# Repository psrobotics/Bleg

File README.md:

# Bleg

Open-source, low cost quadruped leg design with BLDC actuator.

## Videos

[Leg](https://www.youtube.com/watch?v=UqaFMdyX_vk)  /  [Reducer](https://www.youtube.com/watch?v=V_eoM8oxp7Y)

## File Structure

* /hardware - CAD, STL exports, CAM file

* /electronic - Motor driver(Odrive v3.6), Main controller brd, Encoder brd

* /sim - V-rep simulation, python wrapper

## Pics

### Reducer

### Encoder

### Motor

### Parts

## Leg assembly

## License
MIT License

## Contact
* Shuang Peng, {shuangpe}@usc.edu

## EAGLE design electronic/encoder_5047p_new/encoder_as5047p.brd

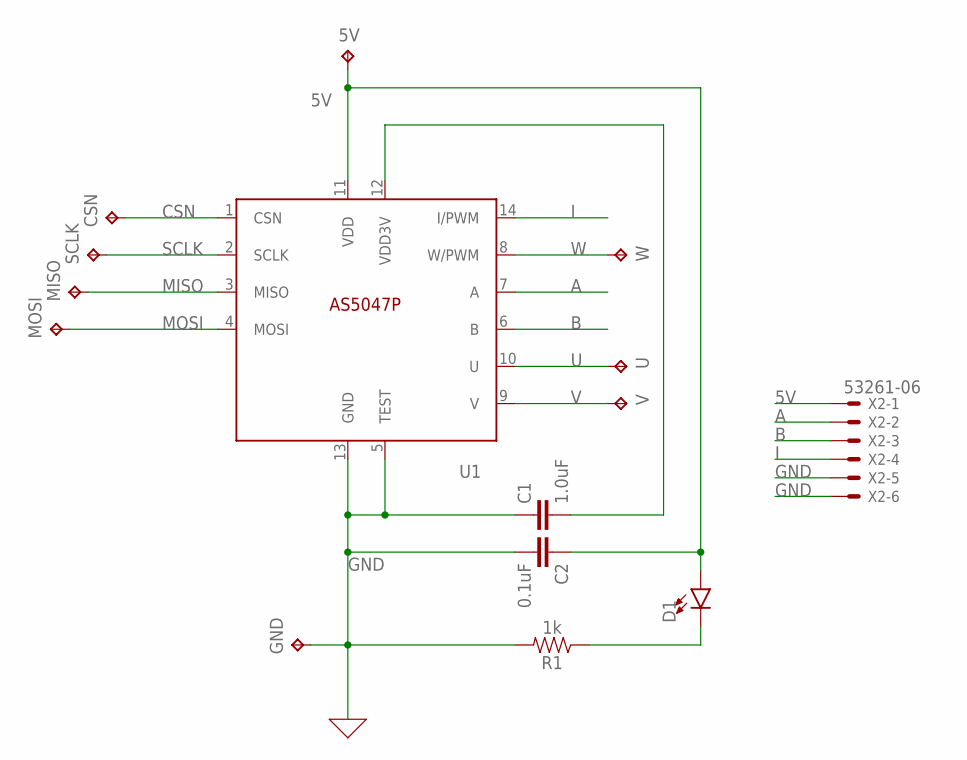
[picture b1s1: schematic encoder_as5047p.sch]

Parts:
5V: TPTP12R; TP12R
C1: 1.0uF; 0603
C2: 0.1uF; 0603
CSN: TPTP12R; TP12R
D1: LED0603; LED-0603
GND: TPTP12R; TP12R
MISO: TPTP12R; TP12R
MOSI: TPTP12R; TP12R
R1: 1k; 0603
SCLK: TPTP12R; TP12R
U: TPTP12R; TP12R
U1: AS5047P; TSSOP14
V: TPTP12R; TP12R
W: TPTP12R; TP12R
X2: 53261-06

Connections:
5V: 5V.TP, C2.1, D1.A, U1.11 (VDD), X2.1
A: U1.7 (A), X2.2
B: U1.6 (B), X2.3
CSN: CSN.TP, U1.1 (CSN)
GND: C1.1, C2.2, GND.TP, R1.2, U1.5 (TEST), U1.13 (GND), X2.5, X2.6
I: U1.14 (I/PWM), X2.4
MISO: MISO.TP, U1.3 (MISO)
MOSI: MOSI.TP, U1.4 (MOSI)
unnamed: C1.2, U1.12 (VDD3V)
unnamed: D1.C, R1.1
SCLK: SCLK.TP, U1.2 (SCLK)
U: U.TP, U1.10 (U)
V: U1.9 (V), V.TP
W: U1.8 (W/PWM), W.TP

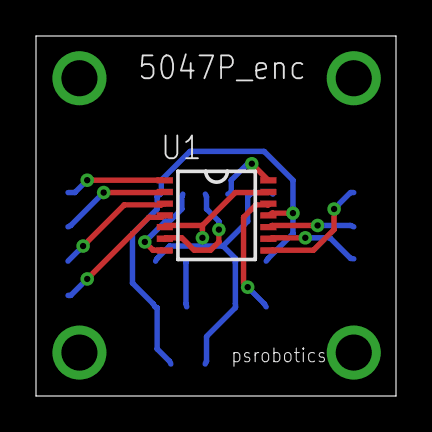
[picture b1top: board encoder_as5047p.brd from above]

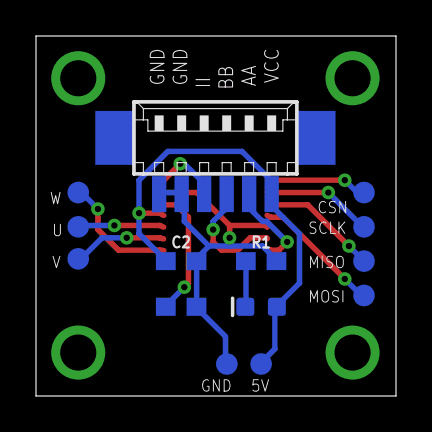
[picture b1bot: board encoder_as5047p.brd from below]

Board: 2 copper layers, 20.0 x 20.0 mm, 15 parts (14 on the bottom side), 14 nets.

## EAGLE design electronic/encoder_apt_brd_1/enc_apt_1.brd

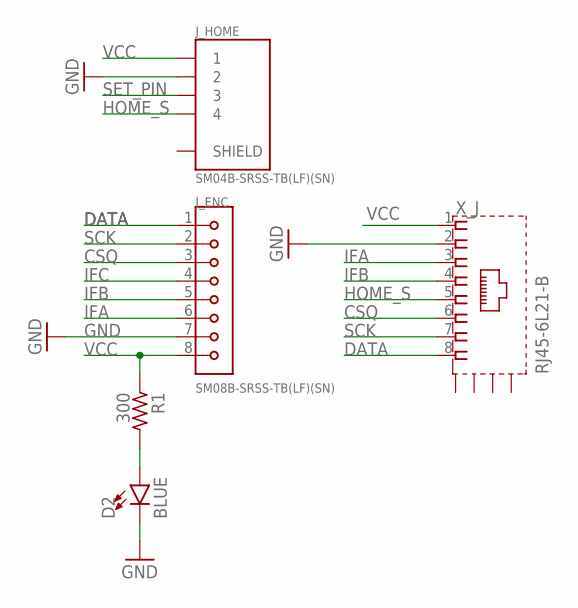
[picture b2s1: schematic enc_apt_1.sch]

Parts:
D2: BLUE; LED-0603
J_ENC: SM08B-SRSS-TB(LF)(SN); JST_SM08B-SRSS-TB(LF)(SN)
J_HOME: SM04B-SRSS-TB(LF)(SN); JST_SM04B-SRSS-TB(LF)(SN)
R1: 300; R0603
X_J: RJ45-6L21-B; RJ45-SHIELD1

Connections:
CSQ: J_ENC.3, X_J.6
DATA: J_ENC.1, X_J.8
GND: D2.C, J_ENC.7, J_HOME.2, X_J.2
HOME_S: J_HOME.4, X_J.5
IFA: J_ENC.6, X_J.3
IFB: J_ENC.5, X_J.4
IFC: J_ENC.4
unnamed: D2.A, R1.2
SCK: J_ENC.2, X_J.7
SET_PIN: J_HOME.3
VCC: J_ENC.8, J_HOME.1, R1.1, X_J.1

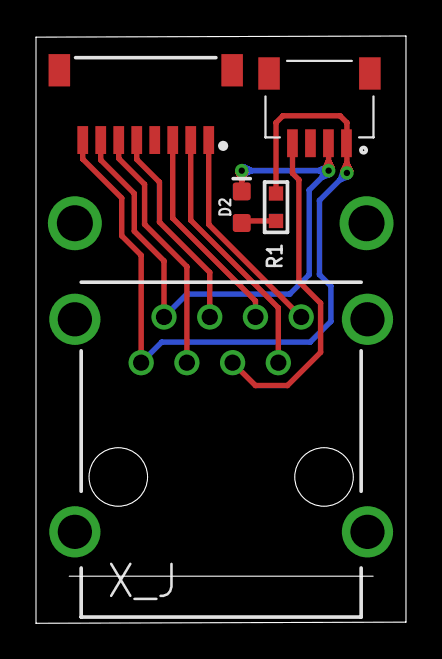
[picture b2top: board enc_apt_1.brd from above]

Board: 2 copper layers, 20.5 x 32.6 mm, 5 parts (0 on the bottom side), 9 nets.

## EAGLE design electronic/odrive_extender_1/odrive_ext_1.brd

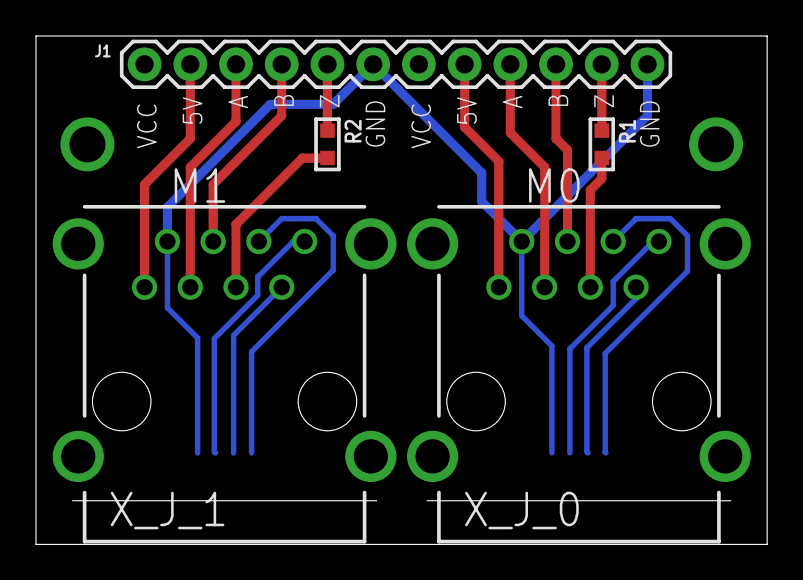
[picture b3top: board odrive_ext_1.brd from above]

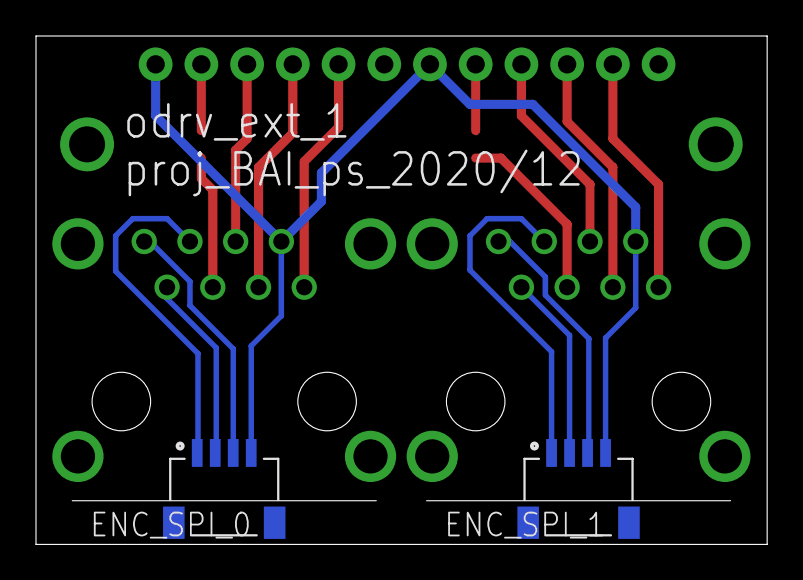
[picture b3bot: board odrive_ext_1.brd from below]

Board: 2 copper layers, 40.6 x 28.2 mm, 7 parts (2 on the bottom side), 17 nets.

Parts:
ENC_SPI_0, ENC_SPI_1: SM04B-SRSS-TB(LF)(SN); JST_SM04B-SRSS-TB(LF)(SN)
J1: 1X12
R1, R2: 0; R0603
X_J_0, X_J_1: RJ45-6L21-B; RJ45-SHIELD1

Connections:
5V_0: J1.8, X_J_0.1
5V_1: J1.2, X_J_1.1
CSQ_0: ENC_SPI_0.1, X_J_0.6
CSQ_1: ENC_SPI_1.1, X_J_1.6
DATA_0: ENC_SPI_0.3, X_J_0.8
DATA_1: ENC_SPI_1.3, X_J_1.8
GND: ENC_SPI_0.4, ENC_SPI_1.4, J1.6, J1.12, X_J_0.2, X_J_1.2
HOME_S_0: R1.2, X_J_0.5
HOME_S_1: R2.2, X_J_1.5
H_0: J1.11, R1.1
H_1: J1.5, R2.1
IFA_0: J1.9, X_J_0.3
IFA_1: J1.3, X_J_1.3
IFB_0: J1.10, X_J_0.4
IFB_1: J1.4, X_J_1.4
SCK_0: ENC_SPI_0.2, X_J_0.7
SCK_1: ENC_SPI_1.2, X_J_1.7

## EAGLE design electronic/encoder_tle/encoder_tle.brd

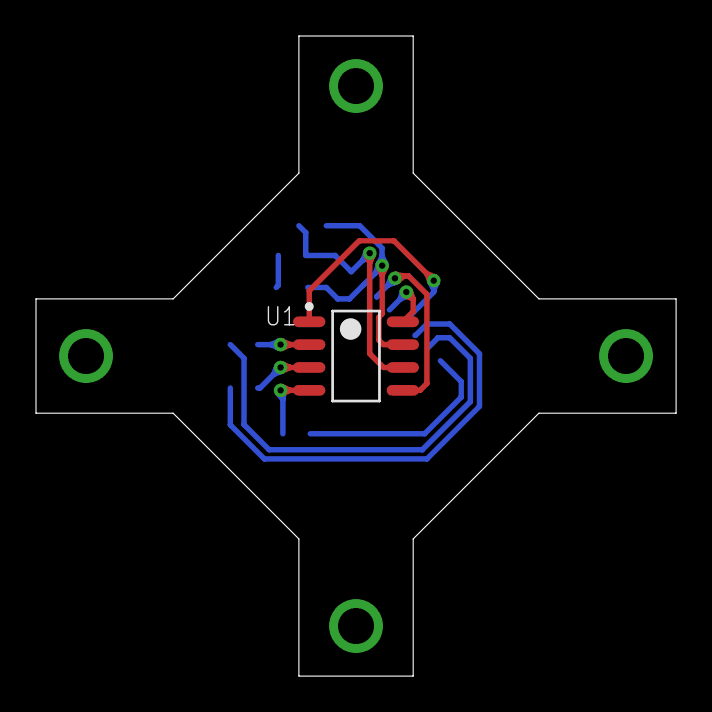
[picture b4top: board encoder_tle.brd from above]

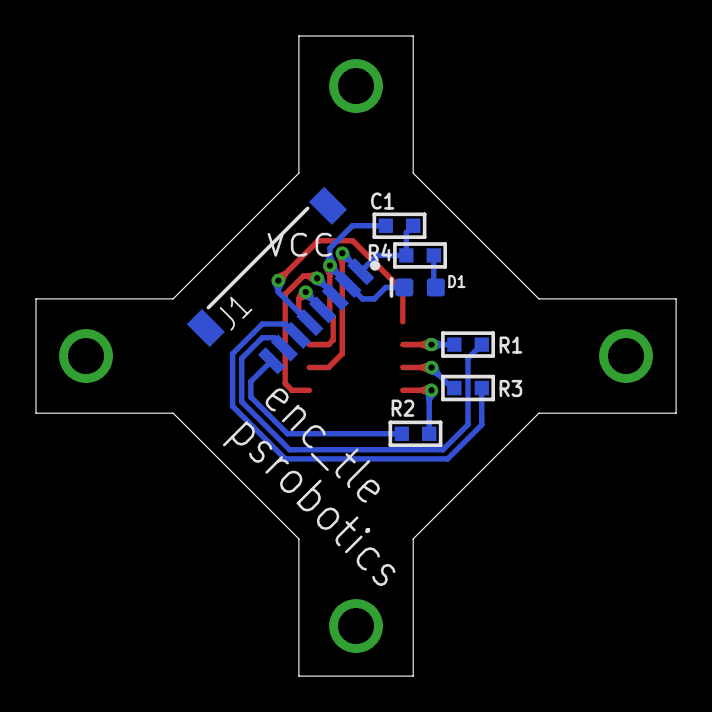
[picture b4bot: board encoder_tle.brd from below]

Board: 2 copper layers, 35.6 x 35.6 mm, 8 parts (7 on the bottom side), 12 nets.

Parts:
C1: 100nf; C0603
D1: BLUE; LED-0603
J1: SM08B-SRSS-TB(LF)(SN); JST_SM08B-SRSS-TB(LF)(SN)
R1, R3: 100; R0603
R2: 470; R0603
R4: 300; R0603
U1: INFINEON_TLE5012B_E1000INFINEON_TLE5012B_E1000_0_1; INFINEON_TLE5012B_E1000_1

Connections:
CSQ: J1.6, R3.1
DATA: J1.8, R2.1
GND: C1.2, D1.C, J1.2, U1.7
IFA: J1.3, U1.5
IFB: J1.4, U1.8
IFC: J1.5, U1.1
unnamed: D1.A, R4.2
unnamed: R3.2, U1.3
unnamed: R2.2, U1.4
unnamed: R1.2, U1.2
SCK: J1.7, R1.1
VCC: C1.1, J1.1, R4.1, U1.6

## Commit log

2024-02-26 Create r
2024-02-26 add: 0226
2024-02-26 fix: 0226 broken index
2024-02-26 add: 0226 - 3
2024-02-26 add: 0226 - 4
2024-02-27 fix: 0227 typo

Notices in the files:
parts and their libraries:
SparkFun-Capacitors: Licensing: Creative Commons ShareAlike 4.0 International - https://creativecommons.org/licenses/by-sa/4.0
rc-master-smd: Copyright (C) 2007, Bob Starr
